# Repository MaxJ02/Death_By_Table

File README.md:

# School project - Autonomous RC-car - ELA22, YRGO

## Introduction

The university of YRGO anually hosts an autonomous rc-car grand prix between the two first year electronic-engineering classes. The classes are split into three
groups per class, where each group is tasked with the goal to design and construct a fully autonomous rc car to compete in the YRGO grand prix of that year.
The car races three competing cars simoultaneously on the track where the car that finishes the most laps in 3 minutes is crowned the winner.
The grand prix consists of a group stage, quarter finals, semi finals and the final.

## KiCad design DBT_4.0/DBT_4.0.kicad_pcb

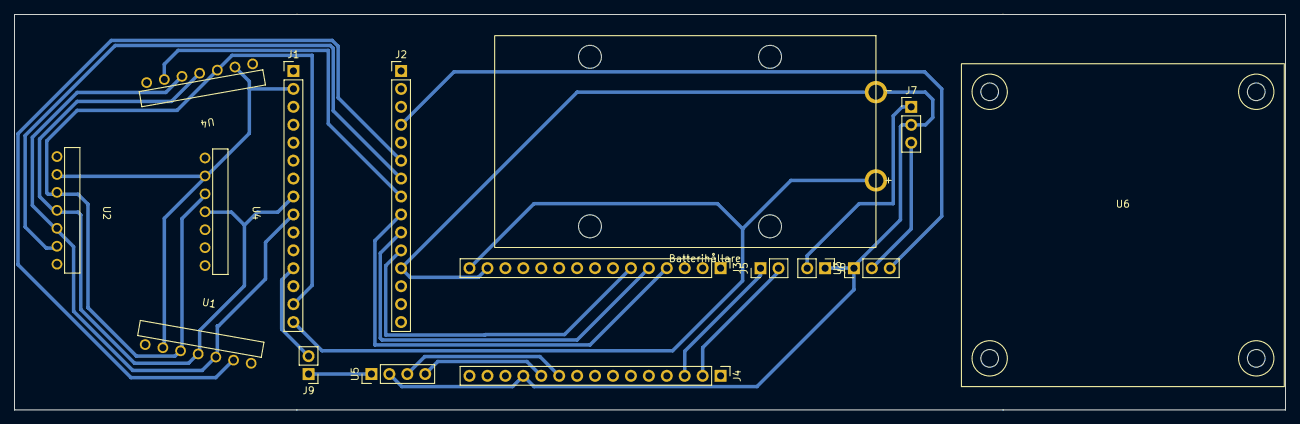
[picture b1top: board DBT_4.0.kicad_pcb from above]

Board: 2 copper layers, 180.0 x 56.0 mm, 16 parts (0 on the bottom side), 29 nets.

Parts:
Batterihållare: Batterihållare_9V_projekt_2
J1, J2, J3, J4: Conn_01x15; PinHeader_1x15_P2.54mm_Vertical
J5, J6, J9: Conn_01x02; PinHeader_1x02_P2.54mm_Vertical
J7: Conn_01x03; PinHeader_1x03_P2.54mm_Vertical
U1, U2, U4, U4#2: VL53L1X; VL53L1x
U3: Servo; PinHeader_1x03_P2.54mm_Vertical
U5: Start_module; PinHeader_1x04_P2.54mm_Vertical
U6: H-brygga

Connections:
+3.3V: J1.2, J3.2, U1.2 (VIN), U2.2 (VIN), U4.2 (VIN), U4#2.2 (VIN)
+5V: J1.12, J3.12, J7.3, J9.2, U3.2 (Vin/+)
+9V: Batterihållare.1, J1.15, J3.15
+BATT: J6.2, J7.1
/*D3: J4.10, U5.3 (Start)
/*D5: J2.8, J4.8, U4.6 (XSHUNT)
/*D6: J2.7, J4.7, U2.6 (XSHUNT)
/*D9: J2.4, J4.4, U3.3 (Signal)
/*D10/SS: J2.3, J4.3, J5.1
/*D11/MOSI: J2.2, J4.2, J5.2
/A0/D4: J2.9, J3.4
/A1/*D3: J2.10, J3.5
/A2/D2: J2.11, J3.6
/A3: J1.7, J3.7
/A4/SDA: J1.8, J3.8, U1.4 (SDA), U2.4 (SDA), U4.4 (SDA), U4#2.4 (SDA)
/A5/SCL: J1.9, J3.9, U1.5 (SCL), U2.5 (SCL), U4.5 (SCL), U4#2.5 (SCL)
/A6: J1.10, J3.10
/A7: J1.11, J3.11
/AREF: J1.3, J3.3
/D0/RX: J2.14, J4.14
/D1/TX: J2.15, J4.15
/D2: J4.11, U5.4 (Kill)
/D7: J2.6, J4.6, U1.6 (XSHUNT)
/D8: J2.5, J4.5, U4#2.6 (XSHUNT)
/D12/MISO: J2.1, J4.1
/D13/SCK: J1.1, J3.1
/~RESET: J1.13, J2.13, J3.13, J4.13
GND: Batterihållare.2, J1.14, J2.12, J3.14, J4.12, J6.1, J7.2, U1.3 (GND), U2.3 (GND), U3.1 (GND/-), U4.3 (GND), U4#2.3 (GND), U5.2 (GND)
unnamed: J9.1, U5.1 (VCC)

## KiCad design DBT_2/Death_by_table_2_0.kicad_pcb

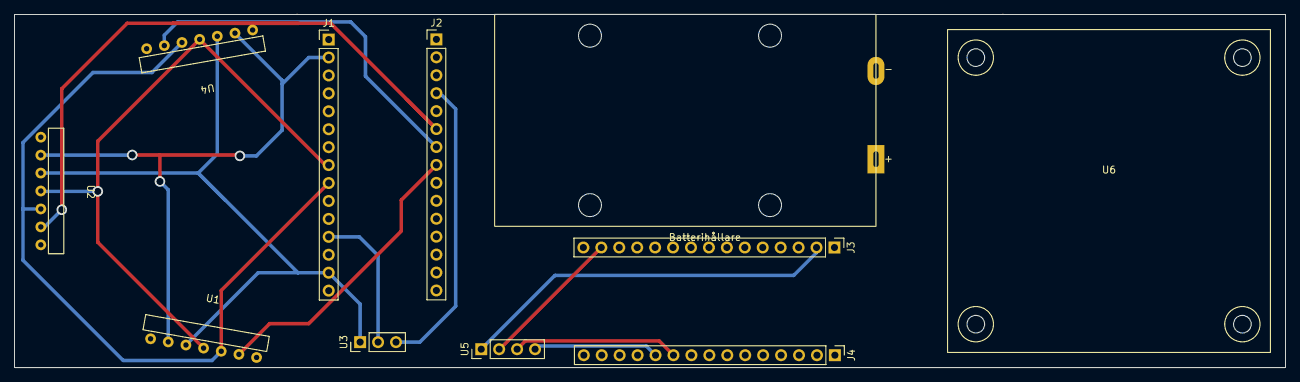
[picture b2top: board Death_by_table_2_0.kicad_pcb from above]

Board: 2 copper layers, 180.0 x 50.0 mm, 11 parts (0 on the bottom side), 28 nets.

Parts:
Batterihållare: Batterihållare_9V_projekt_2
J1, J2, J3, J4: Conn_01x15; PinHeader_1x15_P2.54mm_Vertical
U1, U2, U4: VL53L1X; VL53L1x
U3: Servo; PinHeader_1x03_P2.54mm_Vertical
U5: Start_module; PinHeader_1x04_P2.54mm_Vertical
U6: H-brygga

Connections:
+3.3V: J1.2, J3.2, U1.2 (VIN), U2.2 (VIN), U4.2 (VIN), U5.1 (VCC)
+5V: J1.12, J3.12, U3.2 (Vin/+)
+6V: J1.15, J3.15
/*D3: J2.10, J4.10, U5.3 (Start)
/*D5: J2.8, J4.8, U1.6 (XSHUNT)
/*D6: J2.7, J4.7, U4.6 (XSHUNT)
/*D9: J2.4, J4.4, U3.3 (Signal)
/*D10/SS: J2.3, J4.3
/*D11/MOSI: J2.2, J4.2
/A0: J1.4, J3.4
/A1: J1.5, J3.5
/A2: J1.6, J3.6
/A3: J1.7, J3.7
/A4/SDA: J1.8, J3.8, U1.4 (SDA), U2.4 (SDA), U4.4 (SDA)
/A5/SCL: J1.9, J3.9, U1.5 (SCL), U2.5 (SCL), U4.5 (SCL)
/A6: J1.10, J3.10
/A7: J1.11, J3.11
/AREF: J1.3, J3.3
/D0/RX: J2.14, J4.14
/D1/TX: J2.15, J4.15
/D2: J2.11, J4.11, U5.4 (Kill)
/D4: J2.9, J4.9
/D7: J2.6, J4.6, U2.6 (XSHUNT), U4.1 (VDD)
/D8: J2.5, J4.5
/D12/MISO: J2.1, J4.1
/D13/SCK: J1.1, J3.1
/~RESET: J1.13, J2.13, J3.13, J4.13
GND: J1.14, J2.12, J3.14, J4.12, U1.3 (GND), U2.3 (GND), U3.1 (GND/-), U4.3 (GND), U5.2 (GND)

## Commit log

2023-03-14 Rename start_module.c to startmodule.c
2023-04-19 Arduino kod
    Läser in sensor värden och styr servo med pid-styrning
2023-04-19 kombinerad styr och drift.
    Styr och sensor fungerar. Men driver inte motorn framåt. Pin 10 stannar låg.
2023-04-22 Reverse och kör signal
    Lade till en reverse funktion som vänder på styrningen när framsensorn känner av ett avstånd på mindre än 20cm i 3 sekunder. Avstånd och tiden borde finjusteras efter test på banan. När reverse varia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
2023-04-27 Rename startmodule.c to startmoduledummy.c
2023-05-04 Update and rename motorkod.ino to drivsystem.ino
    Updated from the current local version
2023-05-05 Döpte om styrsystemskoden
2023-05-05 Update drivsystem.ino
    några nya funktioner.
2023-05-07 DBT_pcb
2023-05-10 Kretskort version 4
    Nytt kort. Ett lager minimerar jumper kablar
2023-05-10 unzippad version av pcb4 för renlighet
2023-05-10 Rename header.h to header.hpp
2023-05-12 Update styrsystem.ino
    Uppdaterad för styrning av bilen med de nya däcken
2023-05-12 Update drivsystem.ino
    Uppdatering av koden för bilens nya däck samt boost.
2023-06-07 Update styrsystem.ino
    Utan back-funktioner
